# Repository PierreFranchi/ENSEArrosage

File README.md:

# ENSEArrosage
Projet de première année à l'ENSEA

Projet 1ère Année à l’ENSEA

Présentation du projet :

Le but de ce projet est de créer un système permettant d’automatiser l’arrosage des 2 murs végétalisés disposés dans la K-fet de l'Ensea.

Pour cela nous disposons de 3 capteurs : un de température et d’humidité de l’air, un de luminosité et un autre mesurant l'humidité du sol. Ces 3 capteurs sont reliés à une STM32, qui elle-même communique avec une Raspberry Pi.
De plus, la Raspberry Pi récupère des données météorologiques depuis une API météo.
Pour finir, un site web, hébergé sur la RPI, permet d’observer en temps réel les données des capteurs et celles provenant de l’API météo mais aussi de contrôler le type d'arrosage des plantes. Ainsi, deux modes sont disponibles : 
- un mode manuel : L’utilisateur peut entrer sur le site une durée d’arrosage. 
- un mode automatique : L’arrosage est géré intelligemment en fonction des données des capteurs et de la météo des jours à venir.

L’acquisition des données météos et des données des capteurs s’effectuent une fois toutes les  6h.

De plus nous devons répondre au cahier des charges suivant :
- Utiliser une RPI
- Disposer de 3 types de capteurs : humidité, luminosité et température
- Travailler avec les données météorologiques en temps réel (API Météo)
- Créer un serveur WEB afin de vérifier l’état du plant et contrôler manuellement l’arrosage.
- Contrôler l’arrivée d’eau

Pour plus de détails, un diaporama de présentation est présent dans le GIT.

Liste du matériel :

- Raspberry pi 4 
- STM32-L476 nucleo
- Capteur Température + Humidité : DHT22 (AM2302)
- Capteur Luminosité : Grove Light Sensor
- Capteur Humidité : Grove Moisture Sensor
- Régulateur de tension 78L05F
- 2 Condensateurs 865060645008 WÜRTH ELEKTRONIK

Liste des logiciels utilisés :

- CUBEIDE pour le code en C
- Eagle pour le schéma électrique et  le PCB
- VS code pour programmer en python, CSS, HTML et SQL

Présentation du contenu du GIT : 

Ce GIT est composé de plusieurs fichiers : 

- Un script bash
- Un dossier comprenant le code en C que nous avons développé sous CubeIDE.
- Un dossier comprenant un site web codé en HTML et en CSS qui nous permet de contrôler l’arrosage et deux codes en python, un pour récupérer les valeurs des capteurs et les données météos et un autre pour lancer le site web.
- Le schéma et le PCB (et la librairie qui va avec) de la carte que nous avons produite.
- Le diaporama que nous avons utilisé pour faire notre présentation.

Tutoriel d’installation :

- Commencer par démarrer la raspberry et la connecter à Internet
- Là, il y a deux options : soit lancer  le script bash afin qu'il télécharge le projet et l'exécute, soit télécharger le projet en entier depuis github
- Faire le montage électrique en suivant le schéma
- Upload le code qui est sur CUBEIDE sur la STM32

NB : Comme l’UART côté RPI ne fonctionnait pas, on a préféré ne pas mettre les commandes d’installation dans le script bash car ce sont peut-être elles qui causent  ce dysfonctionnement.

NB2 : On a décidé d’anonymiser le projet ou cas où il serait rendu public.

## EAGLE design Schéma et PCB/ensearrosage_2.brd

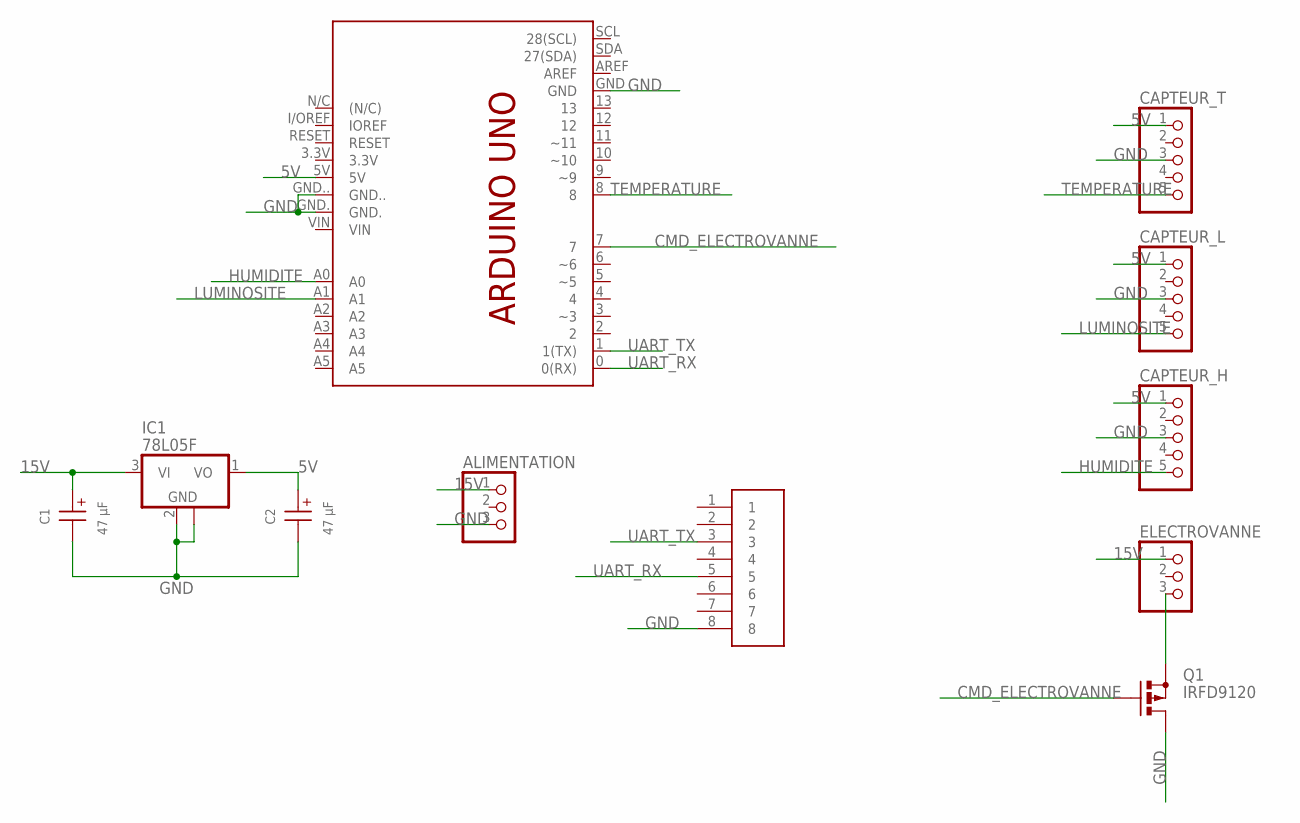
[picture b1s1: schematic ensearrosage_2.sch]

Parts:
ALIMENTATION: PINHD-1X3; 1X03
C1, C2: 47 µF; WCAP-ASLI_5X5.5(DXL)
CAPTEUR_H: PINHD-1X5; 1X05
CAPTEUR_L: PINHD-1X5; 1X05
CAPTEUR_T: PINHD-1X5; 1X05
ELECTROVANNE: PINHD-1X3; 1X03
IC1: 78L05F; SOT89
PCB1: ARDUINO_UNO
Q1: IRFD9120; C370-01
U$2: RJ45

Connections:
5V: C2.1 (+), CAPTEUR_H.1, CAPTEUR_L.1, CAPTEUR_T.1, IC1.1 (VO), PCB1.5V
15V: ALIMENTATION.1, C1.1 (+), ELECTROVANNE.1, IC1.3 (VI)
CMD_ELECTROVANNE: PCB1.7, Q1.G
GND: ALIMENTATION.3, C1.2 (-), C2.2 (-), CAPTEUR_H.3, CAPTEUR_L.3, CAPTEUR_T.3, IC1.2 (GND), IC1.2@1 (GND), PCB1.GND, PCB1.GND., PCB1.GND.., Q1.D, Q1.D1 (D), U$2.8
HUMIDITE: CAPTEUR_H.5, PCB1.A0
LUMINOSITE: CAPTEUR_L.5, PCB1.A1
unnamed: ELECTROVANNE.3, Q1.S
TEMPERATURE: CAPTEUR_T.5, PCB1.8
UART_RX: PCB1.0 (0(RX)), U$2.5
UART_TX: PCB1.1 (1(TX)), U$2.3

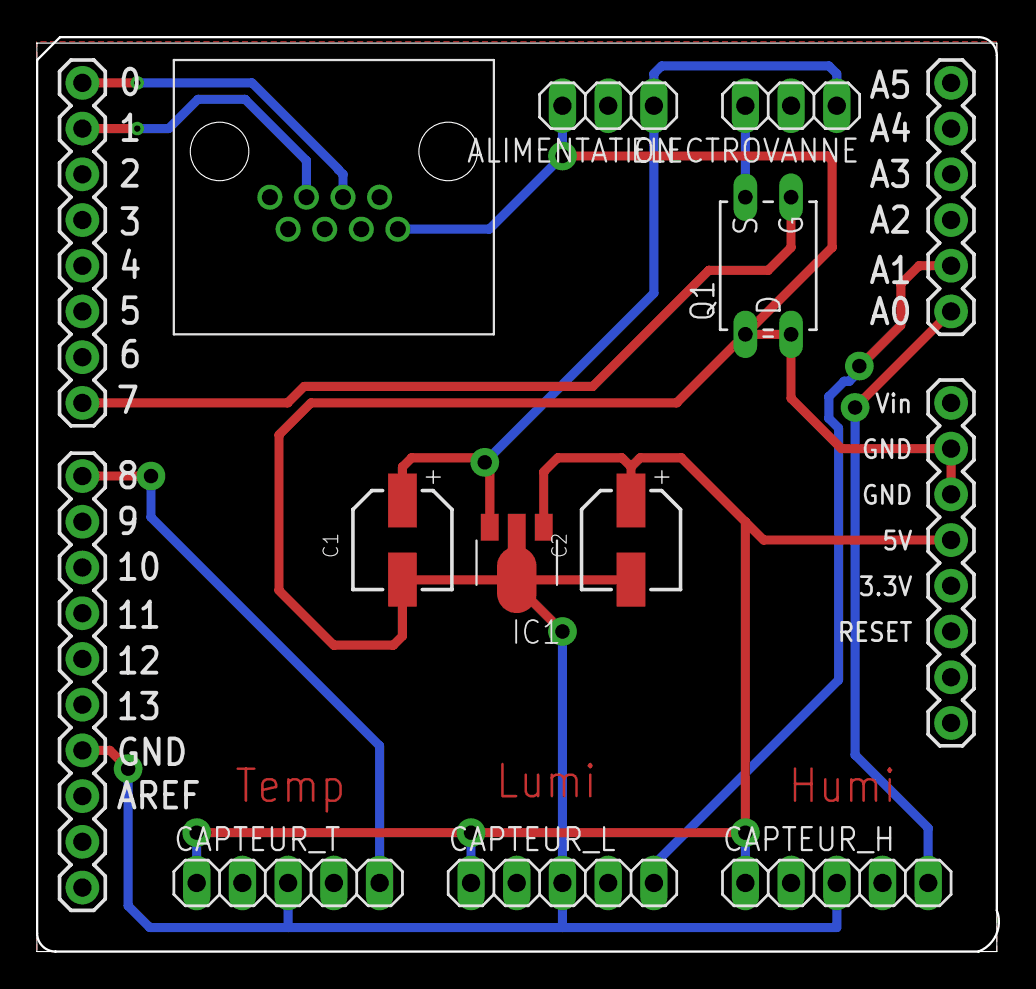
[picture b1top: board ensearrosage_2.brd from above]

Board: 2 copper layers, 53.4 x 50.8 mm, 11 parts (0 on the bottom side), 10 nets.

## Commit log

2021-06-14 Create X

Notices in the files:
parts and their libraries:
Eagle_WCAP-ASLI: Copyright: Würth Elektronik
